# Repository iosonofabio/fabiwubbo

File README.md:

A wireless 38 key keyboard: a variation of the [Wubbo](https://github.com/cacheworks/Wubbo).

### [Interactive Bill of materials](https://iosonofabio.github.io/fabiwubbo/)

The following does not work for this keyboard yet... we'll get there someday hopefully.
### [Example ZMK config repo](https://github.com/mveerd/wubbo-zmk-config)

---
**NOTE:** The main PCB kicad files are where development is at now. No bottom or top plates and other things have been adapted yet.

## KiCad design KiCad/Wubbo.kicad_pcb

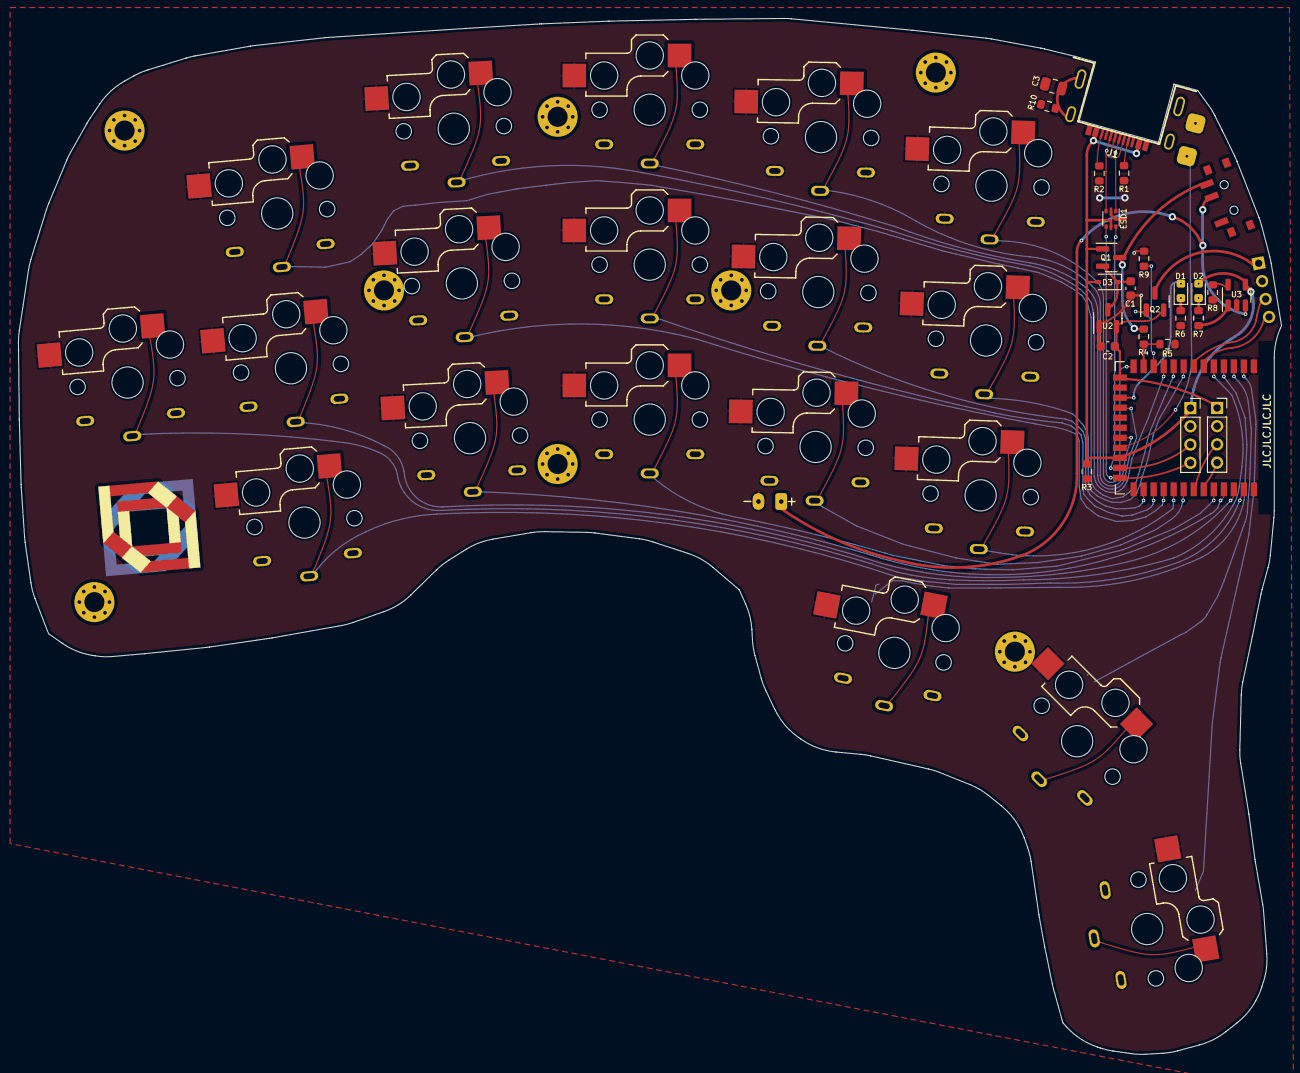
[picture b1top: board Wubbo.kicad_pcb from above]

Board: 2 copper layers, 138.6 x 113.7 mm, 51 parts (1 on the bottom side), 41 nets.

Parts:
C1, C2: 1uF; C_0603_1608Metric
C3: 4.7n; C_0805_2012Metric
D1: Blue LED; LED_0603_1608Metric_shinethrough
D2: Red LED; LED_0603_1608Metric
D3: D_Schottky; D_SOD-323
ESD1: USBLC6-2P6; SOT-666
GR1, GR2: 9b7f651c-c6a4-4f53-b457-ec411c8fc700
J1: USB_C_Receptacle; USB-C-12-Pin-MidMount
J2: SWD; PinSocket_1x04_P2.00mm_Vertical
J3: USB; PinSocket_1x04_P2.00mm_Vertical
J4: JST-BATT; JST_PH_S2B-PH-K_1x02_P2.00mm_Horizontal
J5: USB; PinHeader_1x04_P2.00mm_Vertical
Q1, Q2: AO3407; SOT-23
R1, R2: 5.1K; R_0603_1608Metric
R3: 100K; R_0603_1608Metric
R4: 806/820k; R_0603_1608Metric
R5, R9: 2M; R_0603_1608Metric
R6, R7: 1K; R_0603_1608Metric
R8: 10K; R_0603_1608Metric
R10: 1M; R_0603_1608Metric
R_TACT1: SW_Push; 3-4-2_micro_tact_switch
SW1, SW2, SW3, SW4, SW5, SW6, SW7, SW8, SW9, SW10, SW11, SW12, SW13, SW14, SW15, SW16, SW17, SW18, SW19: Choc; PG13500-reversible
SW_POW1: SW_SPDT; SW_SPDT_PCM12
TENT1: Tenting Puck; Tenting_Puck
U1: nRF52840_holyiot_18010
U2: XC6206P LDO; SOT-23
U3: LTC4054ES5-4.2; TSOT-23-5

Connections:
+3V3: C2.1, J2.1, Q2.2 (S), U1.14 (VDD_nRF), U2.2 (VO)
+BATT: J4.1, SW_POW1.2 (B), U3.3 (BAT)
/BAT+_SWITCHED: Q1.3 (D), R4.1, SW_POW1.3 (C)
/Net-(U3-PROG): R8.2, U3.5 (PROG)
/V-IN: C1.1, D3.1 (K), Q1.2 (S), U2.3 (VI)
BLUE_LED: D1.2 (A), U1.16 (P1.09)
D+: ESD1.4 (I/O2), J3.4, U1.24 (D+)
D-: ESD1.6 (I/O1), J3.3, U1.23 (D-)
EXT_VCC: J5.1, Q2.3 (D)
Earth: C3.2, R10.2
GND: C1.2, C2.2, C3.1, ESD1.2 (GND), J2.2, J3.2, J4.2, J5.2, R1.2, R2.2, R3.2, R5.2, R6.2, R8.1, R9.2, R10.1, R_TACT1.2, SW1.2, SW2.2, SW3.2, SW4.2, SW5.2, SW6.2, SW7.2, SW8.2, SW9.2, SW10.2, SW11.2, SW12.2, SW13.2, SW14.2, SW15.2, SW16.2, SW17.2, SW18.2, SW19.2, U1.1 (GND), U1.25 (GND), U1.37 (GND), U2.1 (GND), U3.2 (GND)
unnamed: D1.1 (K), R6.1
unnamed: D2.1 (K), R7.1
unnamed: R7.2, U3.1 (~CHRG)
P0.02: J5.3, U1.7 (P0.02)
P0.03: J5.4, U1.6 (P0.03)
RESET: R_TACT1.1, U1.21 (P0.18/RESET)
SW1: SW1.1, U1.5 (P1.15)
SW2: SW2.1, U1.10 (P0.30)
SW3: SW3.1, U1.17 (P0.12)
SW4: SW4.1, U1.20 (P0.19)
SW5: SW5.1, U1.13 (P0.05)
SW6: SW6.1, U1.35 (P0.09)
SW7: SW7.1, U1.28 (P1.03)
SW8: SW8.1, U1.27 (P1.00)
SW9: SW9.1, U1.26 (P0.22)
SW10: SW10.1, U1.8 (P0.28)
SW11: SW11.1, U1.36 (P0.10)
SW12: SW12.1, U1.34 (P1.06)
SW13: SW13.1, U1.33 (P1.04)
SW14: SW14.1, U1.30 (P1.02)
SW15: SW15.1, U1.29 (P1.01)
SW16: SW16.1, U1.4 (P1.13)
SW17: SW17.1, U1.3 (P1.10)
SW18: SW18.1, U1.2 (P1.11)
SW19: SW19.1, U1.9 (P0.29)
SWDCLK: J2.3, U1.31 (SWDCLK)
SWDIO: J2.4, U1.32 (SWDIO)
VBUS: D2.2 (A), D3.2 (A), ESD1.5 (VBUS), J3.1, Q1.1 (G), R3.1, U1.22 (VBUS), U3.4 (VCC)
VCC_CONTROL: Q2.1 (G), R9.1, U1.11 (P0.31)
VSENSE: R4.2, R5.1, U1.12 (P0.04)

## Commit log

2024-05-14 Various modifications to make it 38 keys
2024-05-14 Remove parts that got lost since the Wubbo
2024-05-14 Typo
2024-05-14 Clarify WIP in README
2024-05-14 Bottom plate for new board shape
2024-05-14 IBOM
2024-05-14 link to ibom in README
